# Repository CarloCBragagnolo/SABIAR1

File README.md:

# SABIAR1

Project files for the Sabiá R1 flight computer

These are the kicad files for the ESP32S3 based flight computer I designed over the summer, Sabiá R1. This is intended as a practise project to improve my skills in programming and pcb design. There are, however, known issues with the design that anyone who uses this design should adress:
first, in the BOM file attached, one of the current limiting/voltage divider resistors in the pyro channels is 7.5 $\ohm$, when it should be 7.5k, causing the led to fail upon arming the pyro channel. Further, the battery voltage measurement circuit was mistakenly connected to a pin with no ADC, so it does not work. Testing is still ongoing so I will keep this page updated.
## DEPENDENCIES
The computer is dependand on the [LIS3MDL](https://github.com/CarloCBragagnolo/lis3mdl) and [LSM6DS3](https://github.com/CarloCBragagnolo/LSM6DS3) libraries, published by myself and available on arduino, as well as the adafruit BMP280 library, also available on arduino. ArduinoEigenDense is also used to handle linear algebra.
## UPDATE 08/10/2026

I have replaced the faulty resistors with the correct valued ones, and this validated the continuity testing, both at the GPIO pin and the LED. Further, the pyros were tested and shown to work, melting through a thin copper wire at 150ms firing time, drawing a estimated 3 amps. No tests have been conducted on a live pyro charge.

Regarding flight software, the attitude kalman filter has been updated to use the magnetometer for up-down facing disambiguation, allowing for accurate logging throughout the flight envelope. Also, the magnetometer can now take both soft and hard iron calibration. The relevant paremeters were calculated using MagMaster. Furthermore, dead-reckoning was added for the y and z axes. This is very much experimental and is not recomended to be used in any flight logic (eg. deploy parachutes early if too far down range).

## TEST FOOTAGE

https://github.com/user-attachments/assets/4542bc1e-f65c-4ce2-99e9-89a8cd237ede

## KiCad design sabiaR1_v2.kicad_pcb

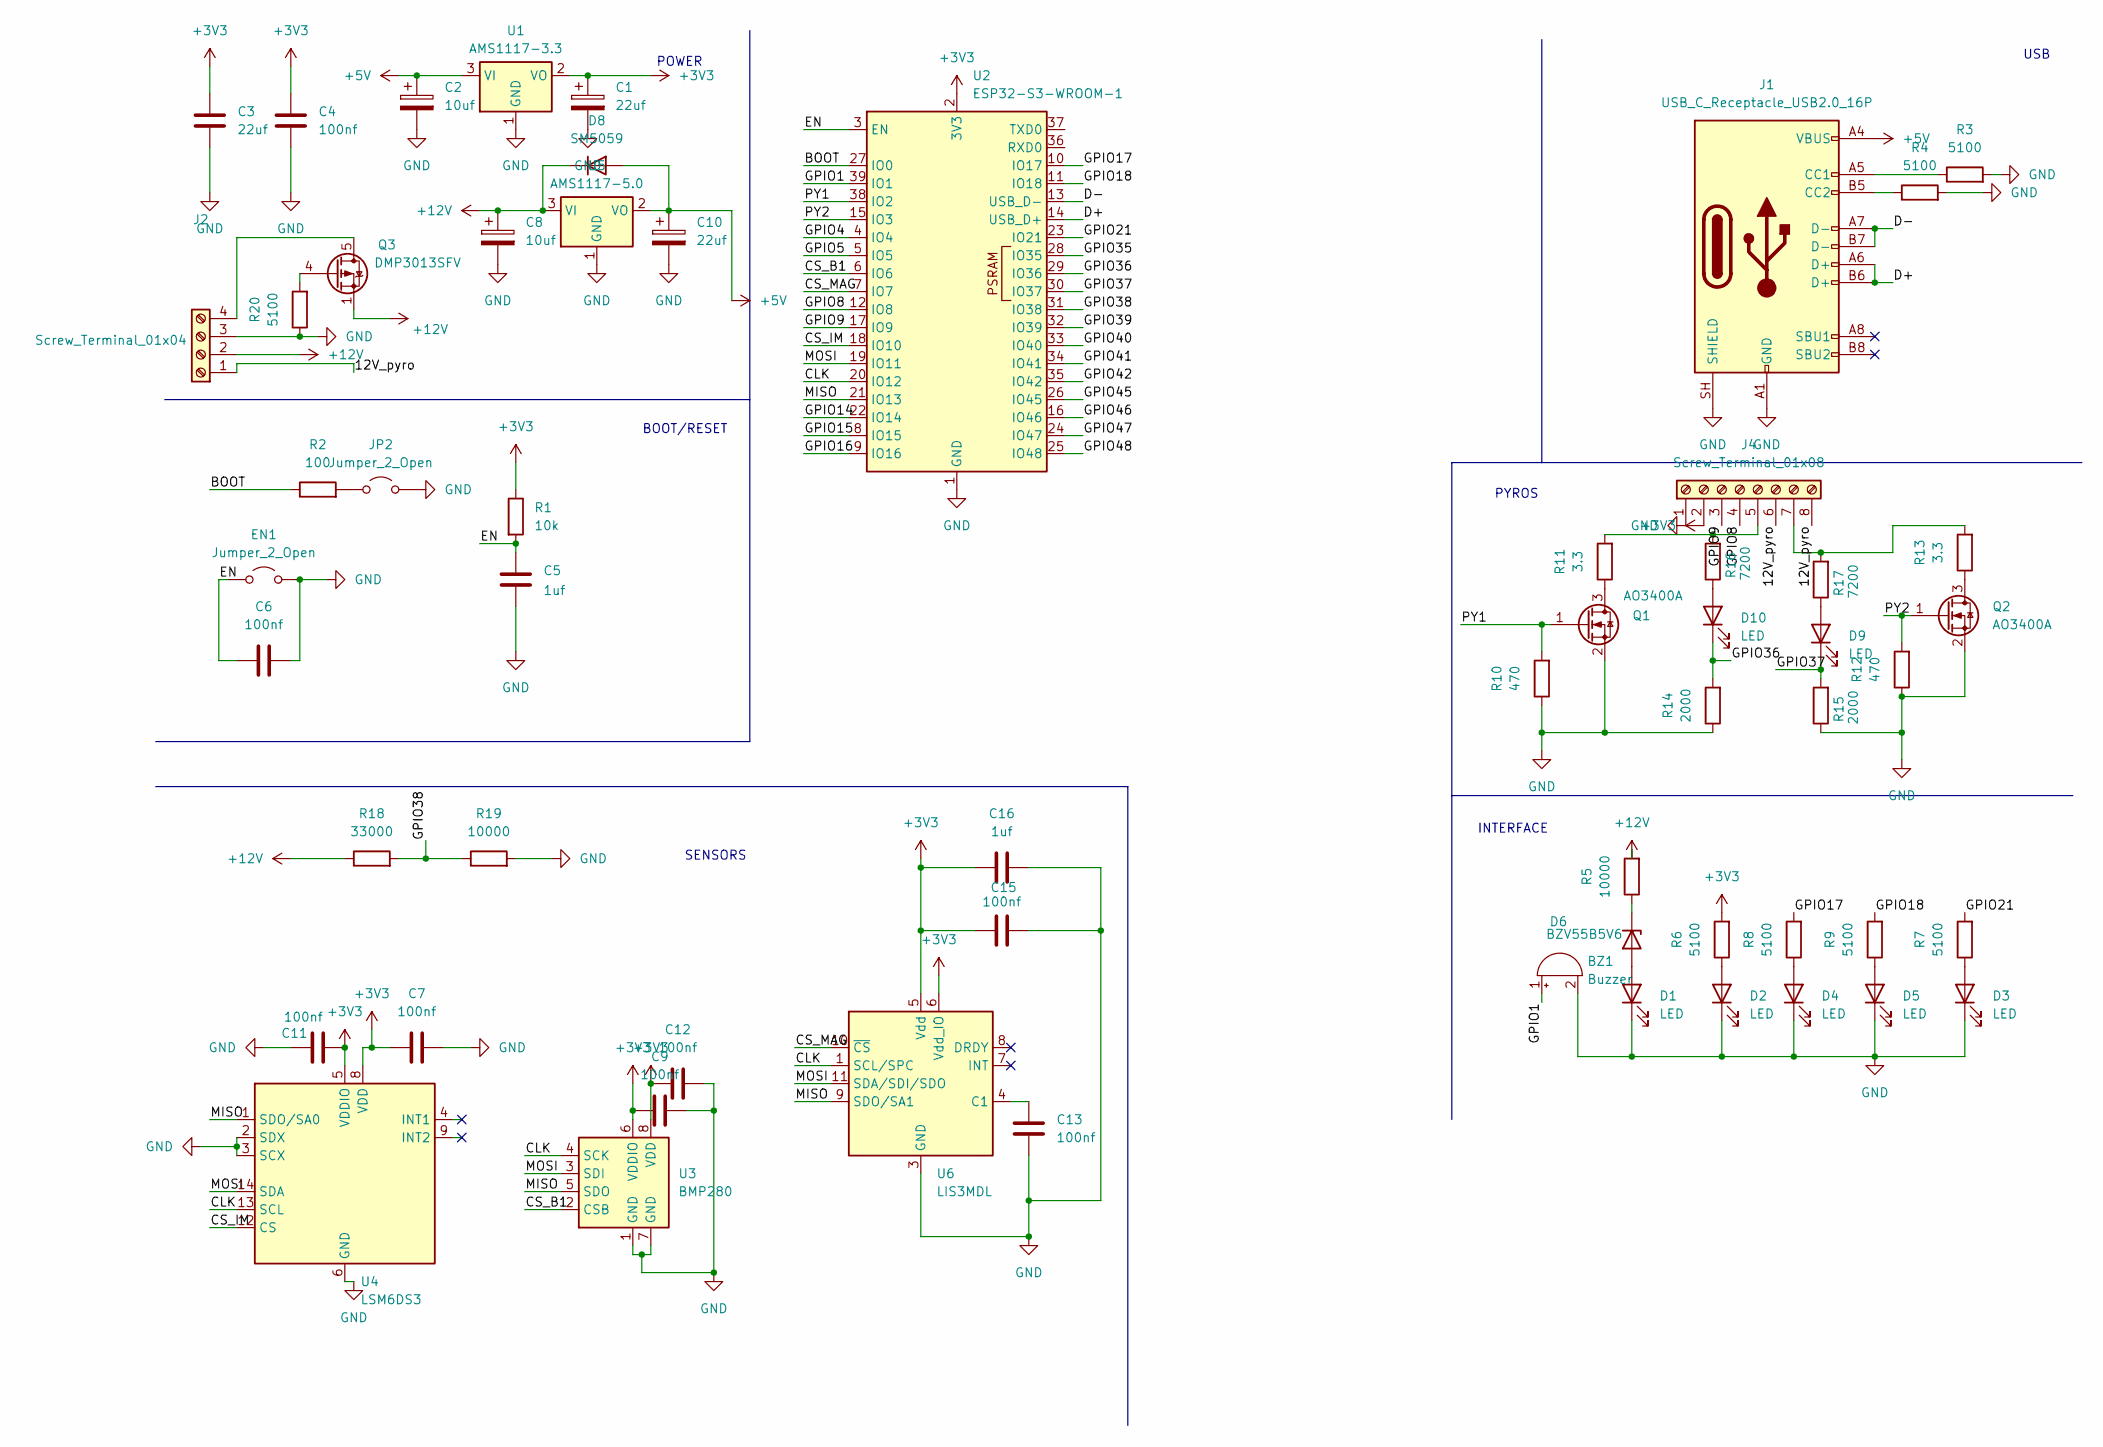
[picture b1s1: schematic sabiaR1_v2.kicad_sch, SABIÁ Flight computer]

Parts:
BZ1: Buzzer; Buzzer_CUI_CPT-9019S-SMT
C1, C10: 22uf; CP_EIA-3216-18_Kemet-A
C2, C8: 10uf; CP_EIA-3216-12_Kemet-S
C3: 22uf; C_0402_1005Metric
C4, C6, C7, C9, C11, C12, C13, C15: 100nf; C_0402_1005Metric
C5, C16: 1uf; C_0402_1005Metric
D1, D2, D3, D4, D5, D9, D10: LED; LED_0603_1608Metric
D6: BZV55B5V6; D_SOD-923
D8: SM5059; D_SOD-123F
EN1: Jumper_2_Open; SolderJumper-2_P1.3mm_Open_Pad1.0x1.5mm
J1: USB_C_Receptacle_USB2.0_16P; USB_C_Receptacle_GCT_USB4105-xx-A_16P_TopMnt_Horizontal
J2: Screw_Terminal_01x04; TerminalBlock_Phoenix_PT-1,5-4-3.5-H_1x04_P3.50mm_Horizontal
J4: Screw_Terminal_01x08; TerminalBlock_Phoenix_PT-1,5-8-3.5-H_1x08_P3.50mm_Horizontal
JP2: Jumper_2_Open; SolderJumper-2_P1.3mm_Open_Pad1.0x1.5mm
Q1, Q2: AO3400A; SOT-23
Q3: DMP3013SFV; Diodes_PowerDI3333-8
R1: 10k; R_0805_2012Metric
R2: 100; R_0805_2012Metric
R3, R4, R6, R7, R8, R9, R20: 5100; R_0805_2012Metric
R5, R19: 10000; R_0805_2012Metric
R10, R12: 470; R_0805_2012Metric
R11, R13: 3.3; R_2010_5025Metric
R14, R15: 2000; R_0805_2012Metric
R16, R17: 7200; R_0805_2012Metric
R18: 33000; R_0805_2012Metric
U1: AMS1117-3.3; SOT-223-3_TabPin2
U2: ESP32-S3-WROOM-1
U3: BMP280; Bosch_LGA-8_2x2.5mm_P0.65mm_ClockwisePinNumbering
U4: LSM6DS3; LGA-14_3x2.5mm_P0.5mm_LayoutBorder3x4y
U5: AMS1117-5.0; SOT-223-3_TabPin2
U6: LIS3MDL; LGA-12_2x2mm_P0.5mm

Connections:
+3V3: C1.1, C3.1, C4.1, C7.1, C9.2, C11.1, C12.2, C15.2, C16.2, J4.2, R1.1, R6.2, U1.2 (VO), U2.2 (3V3), U3.6 (VDDIO), U3.8 (VDD), U4.5 (VDDIO), U4.8 (VDD), U6.5 (Vdd), U6.6 (Vdd_IO)
+5V: C2.1, C10.1, D8.2 (A), J1.A4 (VBUS), J1.A9 (VBUS), J1.B4 (VBUS), J1.B9 (VBUS), U1.3 (VI), U5.2 (VO)
+12V: C8.1, D8.1 (K), J2.2, Q3.1 (S), Q3.2 (S), Q3.3 (S), R5.2, R18.1, U5.3 (VI)
/12V_pyro: J2.1, J4.6, J4.8
/BOOT: R2.1, U2.27 (IO0)
/CLK: U2.20 (IO12), U3.4 (SCK), U4.13 (SCL), U6.1 (SCL/SPC)
/CS_B1: U2.6 (IO6), U3.2 (CSB)
/CS_IM: U2.18 (IO10), U4.12 (CS)
/CS_MAG: U2.7 (IO7), U6.10 (~CS)
/D+: J1.A6 (D+), J1.B6 (D+), U2.14 (USB_D+)
/D-: J1.A7 (D-), J1.B7 (D-), U2.13 (USB_D-)
/EN: C5.1, C6.1, EN1.1 (A), R1.2, U2.3 (EN)
/GPIO1: BZ1.1 (+), U2.39 (IO1)
/GPIO4: U2.4 (IO4)
/GPIO5: U2.5 (IO5)
/GPIO8: J4.4, U2.12 (IO8)
/GPIO9: J4.3, U2.17 (IO9)
/GPIO14: U2.22 (IO14)
/GPIO15: U2.8 (IO15)
/GPIO16: U2.9 (IO16)
/GPIO17: R8.2, U2.10 (IO17)
/GPIO18: R9.2, U2.11 (IO18)
/GPIO21: R7.2, U2.23 (IO21)
/GPIO35: U2.28 (IO35)
/GPIO36: D10.1 (K), R14.2, U2.29 (IO36)
/GPIO37: D9.1 (K), R15.2, U2.30 (IO37)
/GPIO38: R18.2, R19.1, U2.31 (IO38)
/GPIO39: U2.32 (IO39)
/GPIO40: U2.33 (IO40)
/GPIO41: U2.34 (IO41)
/GPIO42: U2.35 (IO42)
/GPIO45: U2.26 (IO45)
/GPIO46: U2.16 (IO46)
/GPIO47: U2.24 (IO47)
/GPIO48: U2.25 (IO48)
/MISO: U2.21 (IO13), U3.5 (SDO), U4.1 (SDO/SA0), U6.9 (SDO/SA1)
/MOSI: U2.19 (IO11), U3.3 (SDI), U4.14 (SDA), U6.11 (SDA/SDI/SDO)
/PY1: Q1.1 (G), R10.2, U2.38 (IO2)
/PY2: Q2.1 (G), R12.2, U2.15 (IO3)
GND: BZ1.2 (-), C1.2, C2.2, C3.2, C4.2, C5.2, C6.2, C7.2, C8.2, C9.1, C10.2, C11.2, C12.1, C13.2, C15.1, C16.1, D1.1 (K), D2.1 (K), D3.1 (K), D4.1 (K), D5.1 (K), EN1.2 (B), J1.A1 (GND), J1.A12 (GND), J1.B1 (GND), J1.B12 (GND), J1.SH (SHIELD), J2.3, J4.1, JP2.2 (B), Q1.2 (S), Q2.2 (S), R3.2, R4.2, R10.1, R12.1, R14.1, R15.1, R19.2, R20.1, U1.1 (GND), U2.1 (GND), U2.40 (GND), U2.41 (GND), U3.1 (GND), U3.7 (GND), U4.2 (SDX), U4.3 (SCX), U4.6 (GND), U4.7 (GND), U5.1 (GND), U6.2 (GND), U6.3 (GND), U6.12 (GND)
unnamed: D1.2 (A), D6.2 (A)
unnamed: D2.2 (A), R6.1
unnamed: D3.2 (A), R7.1
unnamed: D4.2 (A), R8.1
unnamed: D5.2 (A), R9.1
unnamed: D6.1 (K), R5.1
unnamed: D9.2 (A), R17.1
unnamed: D10.2 (A), R16.1
unnamed: J1.A5 (CC1), R3.1
unnamed: J1.B5 (CC2), R4.1
unnamed: J2.4, Q3.5 (D)
unnamed: J4.5, R11.2, R16.2
unnamed: J4.7, R13.2, R17.2
unnamed: JP2.1 (A), R2.2
unnamed: Q1.3 (D), R11.1
unnamed: Q2.3 (D), R13.1
unnamed: Q3.4 (G), R20.2
unnamed: C13.1, U6.4 (C1)

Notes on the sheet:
SENSORS
PYROS
USB
BOOT/RESET
POWER
INTERFACE

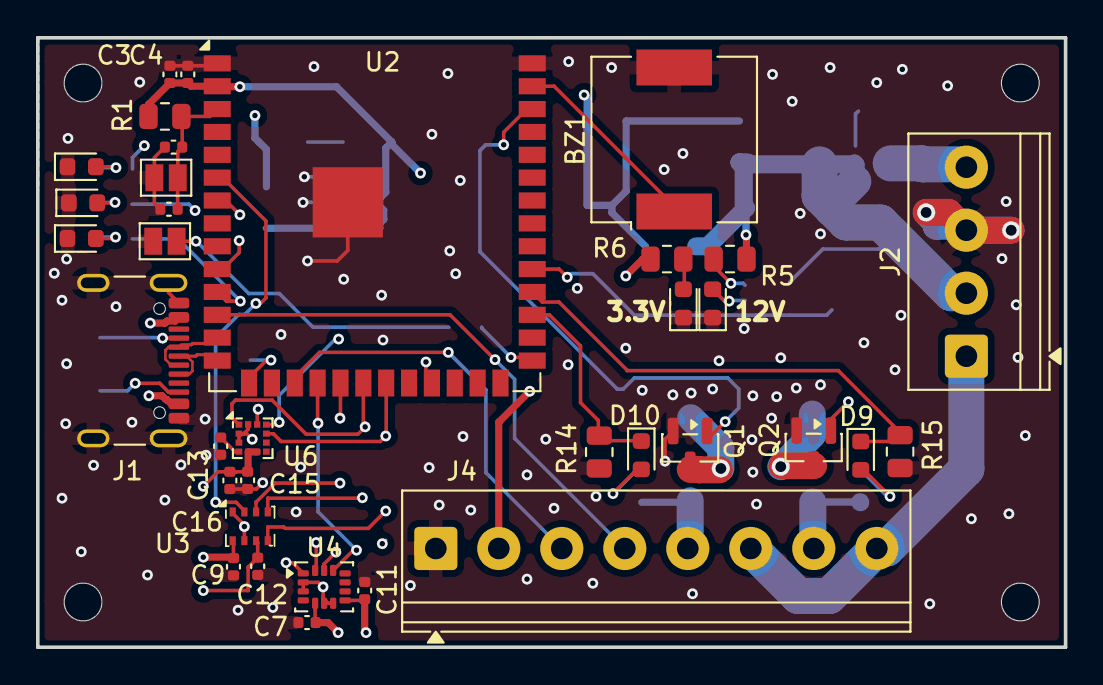
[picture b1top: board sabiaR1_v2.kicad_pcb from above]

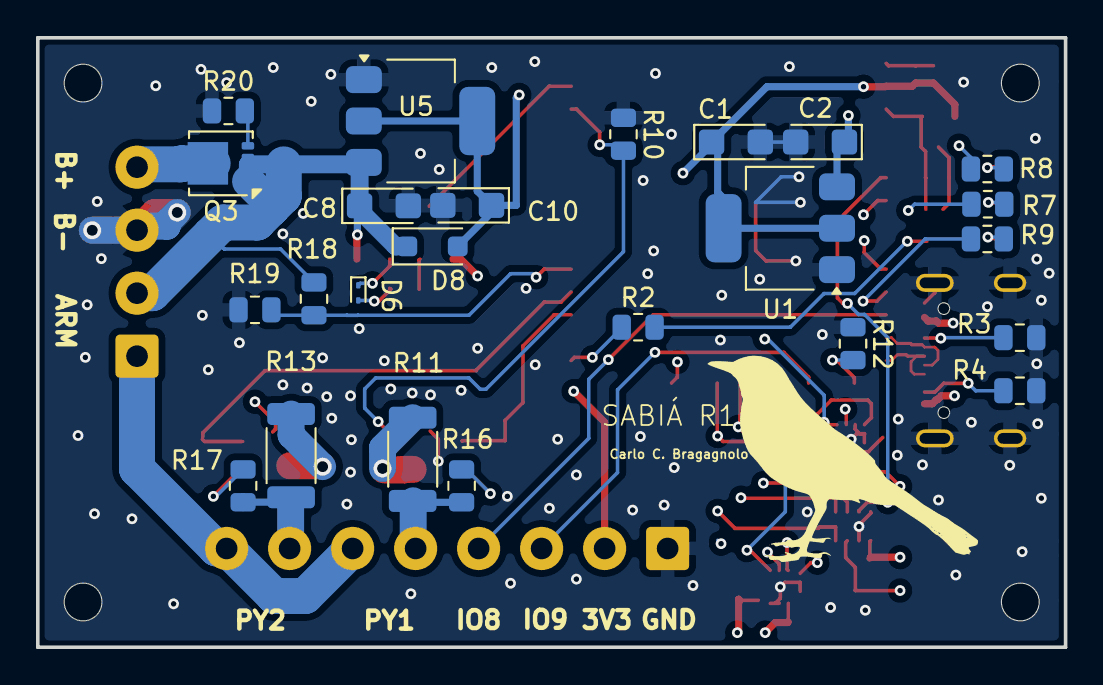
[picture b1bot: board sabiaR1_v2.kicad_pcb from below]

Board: 4 copper layers, 57.1 x 33.9 mm, 59 parts (24 on the bottom side), 44 nets.
